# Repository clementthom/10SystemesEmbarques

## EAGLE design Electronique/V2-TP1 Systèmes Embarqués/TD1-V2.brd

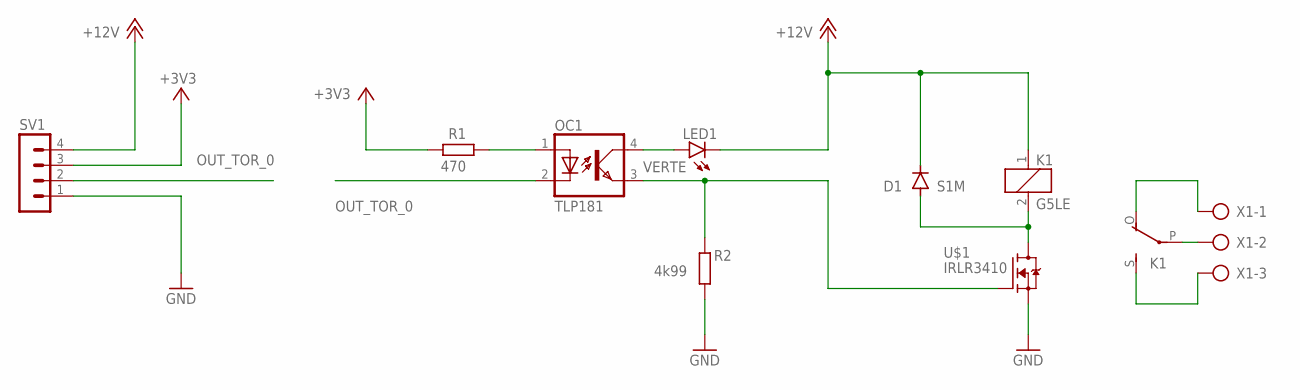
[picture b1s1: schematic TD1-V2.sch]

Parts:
D1: S1M; SMA
K1: G5LE
LED1: VERTE; LED5MM
OC1: TLP181; SO-4
R1: 470; 0204/7
R2: 4k99; 0204/7
SV1: MA04-1
U$1: IRLR3410; TO252
X1: AK300/3

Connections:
+3V3: R1.2, SV1.3
+12V: D1.C, K1.1, LED1.K (C), SV1.4
GND: R2.2, SV1.1, U$1.3 (S)
unnamed: OC1.1 (A), R1.1
unnamed: LED1.A, OC1.4 (COL)
unnamed: OC1.3 (EMIT), R2.1, U$1.1 (G)
unnamed: D1.A, K1.2, U$1.4 (D)
unnamed: K1.P, X1.2
unnamed: K1.O, X1.1
unnamed: K1.S, X1.3
OUT_TOR_0: OC1.2 (C), SV1.2

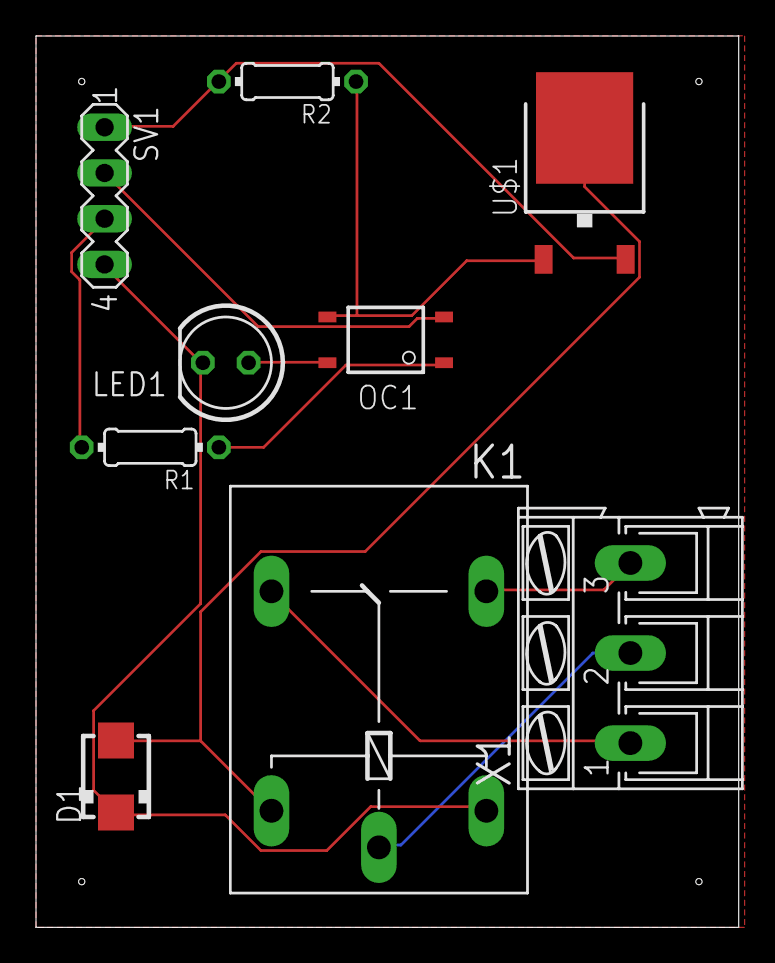
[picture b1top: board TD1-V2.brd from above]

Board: 2 copper layers, 39.0 x 49.5 mm, 9 parts (0 on the bottom side), 11 nets.

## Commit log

2025-02-05 Création du dossier TD1 Création du fichier TD1.c Avancée du TD jusqu'à l'exercice 4
2025-02-05 TD terminé
    Issue : exercice 4 non résolu
2025-02-05 Problème de l'exercice 4 résolu, TD vraiment fini.
2025-02-05 Reconfiguration du répertoire Création de la partie électronique Création du dossier TP1 Création du projet Eagle TP1
2025-02-05 Création du dossier TP1 pour plus d'organisation Création du fichier board du TP1 Avancée du TP1 jusqu'au plan de masse (des 2 couches)
2025-02-21 - TD2 de programmation C fini
2025-02-24 - Création du projet EAGLE V2-TP1, qui est une reprise complète du TP1 --> sera considéré comme le TP1 final - TP1 fini : schematics, board (avec plan de masse), Gerber, BOM
2025-03-03 - ajout des bibliothèques pour le TP2-3 dans le dossier Librairies - création du projet EAGLE TP2-3
2025-03-03 - Fin TP2 - EAGLE Linux plante : passage sur EAGLE Windows - Composants placés hors condensateurs (microC, EEPROM, résistance fixe)
2025-04-07 - Programmation : TD3 presque fini, exercice 8 à débugger - électronique/embarqué : TD4 et 5 persque finis, terminer les fonctions du terminal et faire un timer --> doit être transférer sur le repo
2025-04-12 - exercice 8 terminé : fin du TD
